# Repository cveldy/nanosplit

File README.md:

# nanosplit

Leverless (Hitbox-style) fighting game controller with a split-hand design using Cherry MX Ultra Low Profile (ULP) switches.

## About

Fully assembled, dimensions are `304 x 124 x 9.8mm` (including bolts and non-slip pads, `8.6mm` without).

Powering this device is OpenStick's excellent [GP2040-CE](https://github.com/OpenStickCommunity/GP2040-CE) gamepad firmware. Please see that repository for information about configuration, console compatibility, and all the rest.

The ultra-short scissor switches used by this controller (which I believe are primarily intended for laptop keyboards) have an extremely tactile action and are somewhat harder to depress than standard Sanwa arcade buttons. This makes their actuation feel very binary (either all-the-way down or all-the-way up), almost the complete opposite of the smooth feel of traditional arcade buttons. Experientially, I have found them to be very divisive: people either love or hate the way they feel. If possible, I recommend trying them (say, by borrowing a friend's MPress Nano at your local) before committing to a full build.

## Creation

If you want to produce one, you will need some parts.

### PCB

- 1x nanosplit PCB, created using the files in the `prod/pcb/` directory with an online PCB prototyping service. (e.g., [JLCPCB](https://jlcpcb.com/).) Productions requires assembly with SMD parts, so you'll need to include the Gerbers, BOM, and CPL files.
  - If you are unfamiliar with this process, I recommend following the PCB ordering steps from [this README](https://github.com/AlpenmeisterCustoms/MeisterboxS).
- 16x Cherry MX Ultra Low Profile Switches. (I used Tactile, but you could use Clicky if you want.)
  - I purchased mine [from this German parts supplier](https://www.reichelt.com/us/en/shop/product/cherry_mx_ultra_low_profile_rgb_pushbutton_module-335042?q=%2Fapi%2Fuser%2FcountrySelect%2Fen%2Fhttps%3A%2F%2Fwww.reichelt.com%2Fde%2Fen%2Fshop%2Fproduct%2Fcherry_mx_ultra_low_profile_rgb_pushbutton_module-335042), though they don't seem to be available at that URL anymore.

### Keycaps

- 16x [MPress Nano Caps](https://paradisearcadeshop.com/collections/mpress-nano) from Paradise Arcade Shop.

### Case

- 1x [3d-Printed Case](./prod/case/nochamfer.stl)
  - I don't personally own a 3d printer, but mine came out pretty nicely using [Craftcloud](https://craftcloud3d.com/) in ABS plastic at 60% infil (though in retrospect I may have chosen 80%).
- 1x each [Acrylic "Washer" Layer](./prod/case/acrylic_layer0_1mm.dxf) and [Acrylic Bottom Panel](./prod/case/acrylic_layer1_1mm.dxf) laser cut from `1mm` acrylic.
  - I ordered these online from [Ponoko](https://www.ponoko.com/) in clear.
- OPTIONAL: Non-slip Feet or Pads.
  - I used a few pieces cut from one of [these rolls of adhesive-backed silicon](https://www.amazon.com/dp/B09VFB7QVF).
- 8x M3-0.5 3.85mm Heat-set Threaded Inserts.
  - I ordered [these exact ones](https://www.amazon.com/dp/B077CL322T).
- 8x M3x6mm Bolts.
  - I ordered [these ultra-thin flat capped bolts](https://www.amazon.com/dp/B0C5M7M6ZM).

### Assembly

- Soldering Equipment.
- M2.5 Allen Key.

### Firmware

- The Latest [GP2040-CE Firmware for the Flatbox Rev4](https://github.com/OpenStickCommunity/GP2040-CE/releases/download/v0.7.11/GP2040-CE_0.7.11_FlatboxRev4.uf2), flashed according to the documentation.
- Pin (Button) Mapping using GP2040-CE's [Web Configurator](https://gp2040-ce.info/#/web-configurator)
  - There is a catch: the firmware assumes a default pin mapping that the nanosplit does not use. Until you've remapped the pins, you must hold down `Fn` (Function) (the bottom-most button in the central line) instead of `S2` (Start) when plugging in the controller to enter the configurator.
  - You could also short those switch contacts to ground manually if you haven't installed the switches yet when setting up the firmware.
  - After updating the pin mapping in the configurator, you'll hold `S2` to while plugging the device in to reach the configurator, like normal.
  - The correct mapping for the nanosplit is shown below.

- This controller makes `A1` (Guide), `A2` (Touchpad), `L3`, and `R3` available via a layer using the `Fn` (Function) switch (the bottom-most of the central 3).
- Shown below are the recommended function mappings, though you may prefer to use your own.

### Art

You can use [this template](./prod/art/template_A3_300dpi.psd) to place artwork into a printable template with outlines showing where to cut. The template is sized to A3 paper and set for 300dpi. Once printed and cut, the art slots between the two acrylic lays on the *bottom* of the controller.

## License

PCB and case designs licensed under [CC BY-SA 4.0](https://creativecommons.org/licenses/by/4.0/).

## Acknowledgments

- [GrooveBob](https://github.com/GroooveBob)'s [Stress](https://github.com/GroooveBob/Stress), which helped inspire this design.
- [Paradise Arcade](https://paradisearcadeshop.com/)'s [MPress Nano](https://paradisearcadeshop.com/products/mpress-nano-leverless-gaming-controller), which helped inspire this design.
- [jfedor2](https://github.com/jfedor2)'s [Flatbox](https://github.com/jfedor2/flatbox), whose RP2040 implementation I recreated. [CC BY-SA 4.0](https://creativecommons.org/licenses/by/4.0/).
- [ruiqimao](https://github.com/ruiqimao)'s [Keyboard PCB Guide](https://github.com/ruiqimao/keyboard-pcb-guide), which led me through the entire PCB creation process.
- [pashutk](https://github.com/pashutk)'s [Cherry_MX_ULP](https://github.com/pashutk/Cherry_MX_ULP) repository and links, whose footprints are present in the PCB design and whose README gave me the confidence to try hand-soldering these normally-SMD switches.
- [Sadek Baroudi](https://github.com/sadekbaroudi)'s [Keyboard Case Design](https://kbd.news/Keyboard-Case-Design-1764.html) article, which showed the process for exporting the PCB into a form usable during case design.
- [OpenStickCommunity](https://github.com/OpenStickCommunity)'s [GP2040-CE](https://github.com/OpenStickCommunity/GP2040-CE), whose firmware makes the silicon useful and whose Discord community was extremely helpful.

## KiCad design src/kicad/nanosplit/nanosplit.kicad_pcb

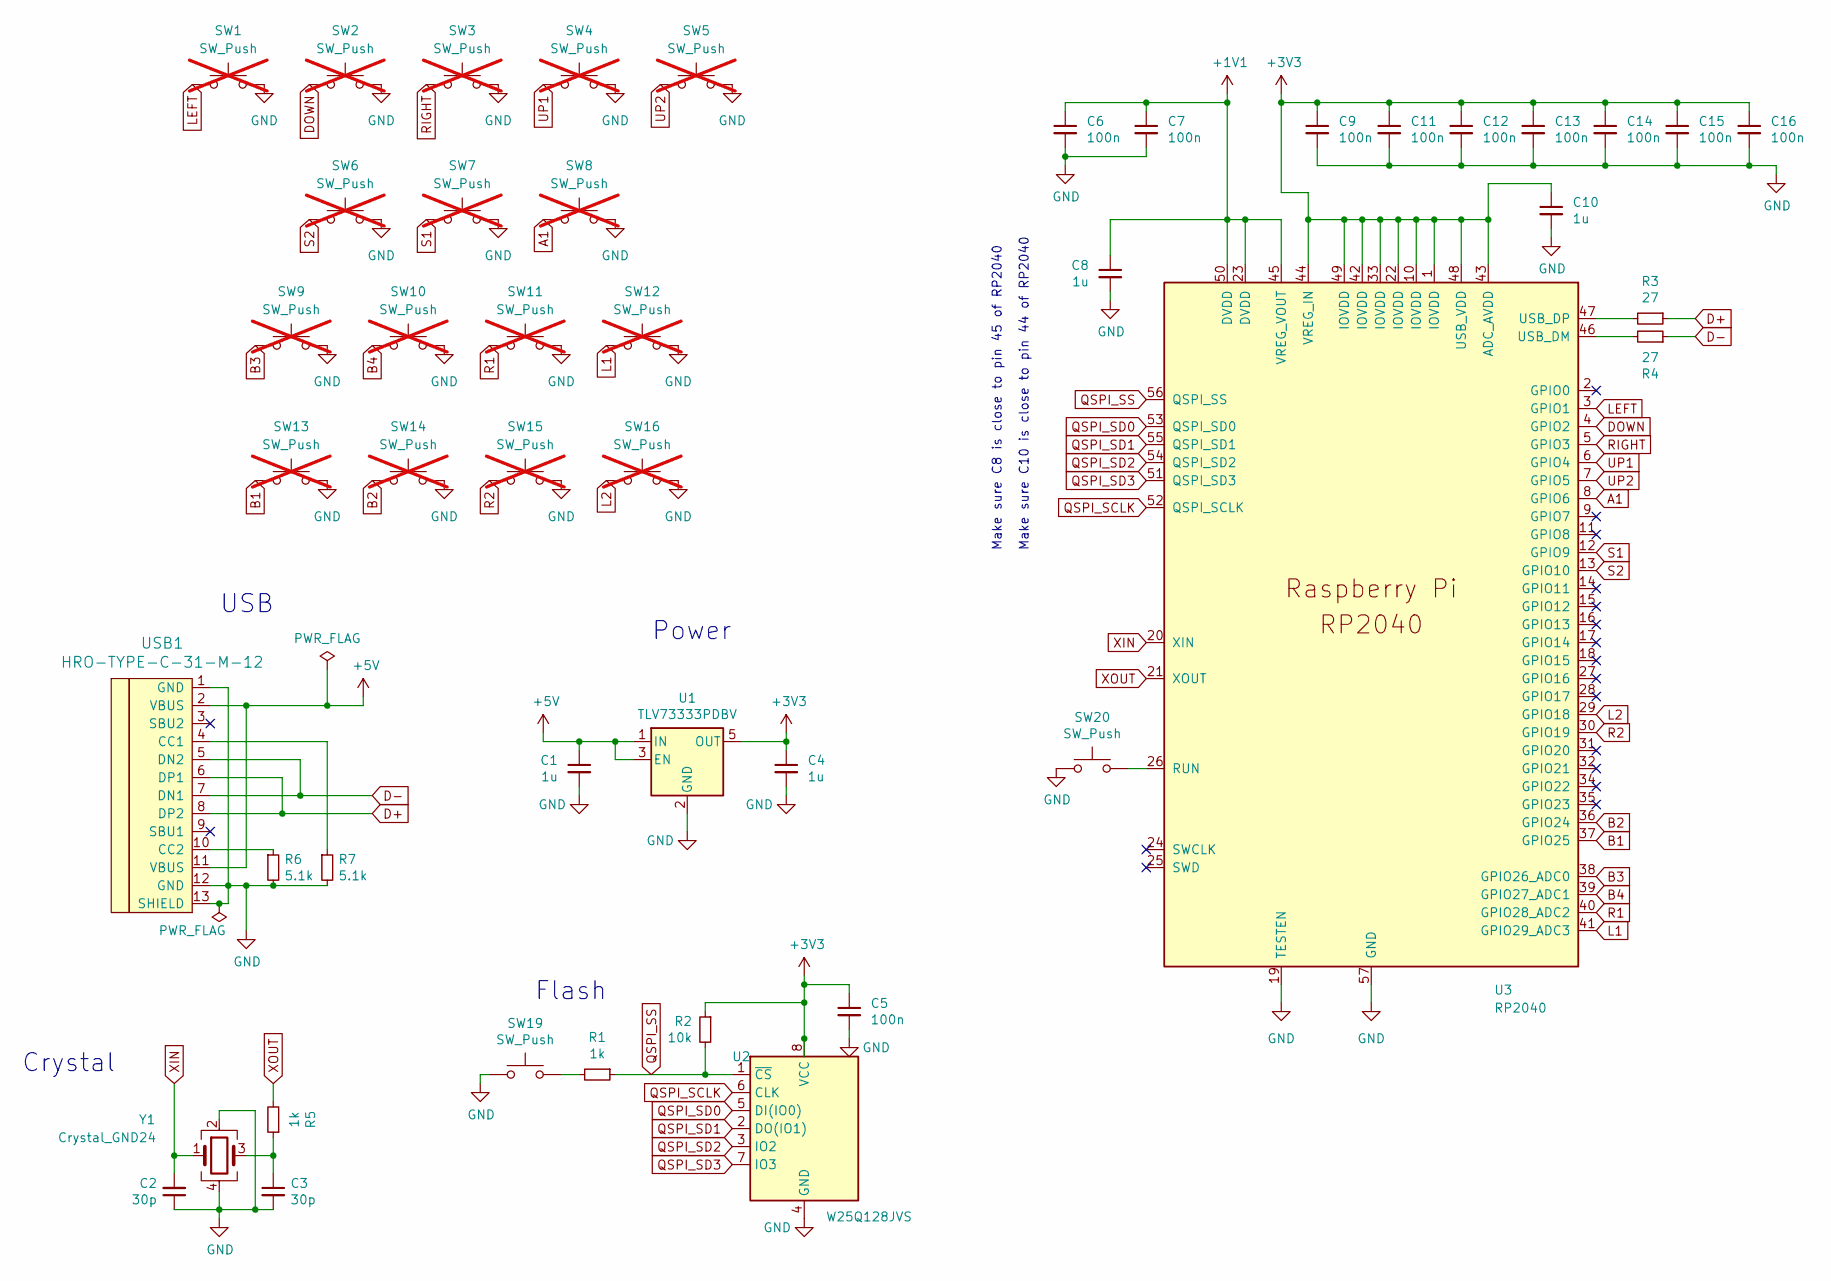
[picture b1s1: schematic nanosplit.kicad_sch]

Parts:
C1, C4, C8, C10: 1u; C_0402_1005Metric; LCSC C52923
C2, C3: 30p; C_0402_1005Metric; LCSC C1570
C5, C6, C7, C9, C11, C12, C13, C14, C15, C16: 100n; C_0402_1005Metric; LCSC C1525
R1, R5: 1k; R_0402_1005Metric; LCSC C11702
R2: 10k; R_0402_1005Metric; LCSC C25744
R3, R4: 27; R_0402_1005Metric; LCSC C138021
R6, R7: 5.1k; R_0402_1005Metric; LCSC C25905
SW1, SW2, SW3, SW4, SW5, SW6, SW7, SW8, SW9, SW10, SW11, SW12, SW13, SW14, SW15, SW16: SW_Push; Cherry_ULP_TH; not fitted
SW19, SW20: SW_Push; SW_SPST_Omron_B3FS-100xP; LCSC C271750
U1: TLV73333PDBV; SOT-23-5; LCSC C134139
U2: W25Q128JVS; SOIC-8_5.23x5.23mm_P1.27mm; LCSC C97521
U3: RP2040; RP2040-QFN-56; LCSC C2040
USB1: HRO-TYPE-C-31-M-12; HRO-TYPE-C-31-M-12-Assembly; LCSC C165948
Y1: Crystal_GND24; Crystal_SMD_3225-4Pin_3.2x2.5mm; LCSC C9002

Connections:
+1V1: C6.1, C7.1, C8.1, U3.23 (DVDD), U3.45 (VREG_VOUT), U3.50 (DVDD)
+3V3: C4.1, C5.1, C9.1, C10.1, C11.1, C12.1, C13.1, C14.1, C15.1, C16.1, R2.1, U1.5 (OUT), U2.8 (VCC), U3.1 (IOVDD), U3.10 (IOVDD), U3.22 (IOVDD), U3.33 (IOVDD), U3.42 (IOVDD), U3.43 (ADC_AVDD), U3.44 (VREG_IN), U3.48 (USB_VDD), U3.49 (IOVDD)
+5V: C1.1, U1.1 (IN), U1.3 (EN), USB1.2 (VBUS), USB1.11 (VBUS)
A1: SW8.1, U3.8 (GPIO6)
B1: SW13.1, U3.37 (GPIO25)
B2: SW14.1, U3.36 (GPIO24)
B3: SW9.1, U3.38 (GPIO26_ADC0)
B4: SW10.1, U3.39 (GPIO27_ADC1)
D+: R3.1, USB1.6 (DP1), USB1.8 (DP2)
D-: R4.1, USB1.5 (DN2), USB1.7 (DN1)
DOWN: SW2.1, U3.4 (GPIO2)
GND: C1.2, C2.1, C3.2, C4.2, C5.2, C6.2, C7.2, C8.2, C9.2, C10.2, C11.2, C12.2, C13.2, C14.2, C15.2, C16.2, R6.2, R7.2, SW1.2, SW2.2, SW3.2, SW4.2, SW5.2, SW6.2, SW7.2, SW8.2, SW9.2, SW10.2, SW11.2, SW12.2, SW13.2, SW14.2, SW15.2, SW16.2, SW19.1, SW20.1, U1.2 (GND), U2.4 (GND), U3.19 (TESTEN), U3.57 (GND), USB1.1 (GND), USB1.12 (GND), USB1.13 (SHIELD), Y1.2, Y1.4
L1: SW12.1, U3.41 (GPIO29_ADC3)
L2: SW16.1, U3.29 (GPIO18)
LEFT: SW1.1, U3.3 (GPIO1)
unnamed: C3.1, R5.1, Y1.3
unnamed: R1.2, SW19.2
unnamed: SW20.2, U3.26 (RUN)
unnamed: R4.2, U3.46 (USB_DM)
unnamed: R3.2, U3.47 (USB_DP)
unnamed: R7.1, USB1.4 (CC1)
unnamed: R6.1, USB1.10 (CC2)
QSPI_SCLK: U2.6 (CLK), U3.52 (QSPI_SCLK)
QSPI_SD0: U2.5 (DI(IO0)), U3.53 (QSPI_SD0)
QSPI_SD1: U2.2 (DO(IO1)), U3.55 (QSPI_SD1)
QSPI_SD2: U2.3 (IO2), U3.54 (QSPI_SD2)
QSPI_SD3: U2.7 (IO3), U3.51 (QSPI_SD3)
QSPI_SS: R1.1, R2.2, U2.1 (~CS), U3.56 (QSPI_SS)
R1: SW11.1, U3.40 (GPIO28_ADC2)
R2: SW15.1, U3.30 (GPIO19)
RIGHT: SW3.1, U3.5 (GPIO3)
S1: SW7.1, U3.12 (GPIO9)
S2: SW6.1, U3.13 (GPIO10)
UP1: SW4.1, U3.6 (GPIO4)
UP2: SW5.1, U3.7 (GPIO5)
XIN: C2.2, U3.20 (XIN), Y1.1
XOUT: R5.2, U3.21 (XOUT)

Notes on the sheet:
USB
Make sure C10 is close to pin 44 of RP2040
Make sure C8 is close to pin 45 of RP2040
Power
Crystal
Flash

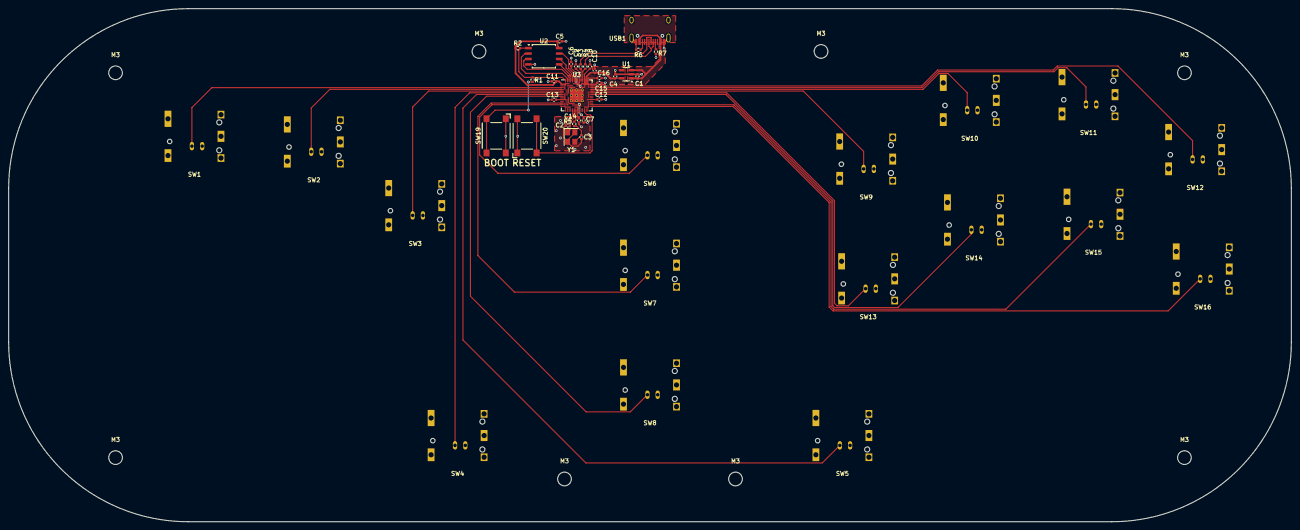
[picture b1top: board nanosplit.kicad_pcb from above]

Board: 2 copper layers, 300.0 x 120.0 mm, 54 parts (0 on the bottom side), 37 nets.

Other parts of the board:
M3, M3#2, M3#3, M3#4, M3#5, M3#6, M3#7, M3#8: MountingHole_3.2mm_M3

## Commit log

2025-01-31 Initial commit, adding important files
2025-01-31 Added mention of license to README
2025-07-13 Added PCB production files!
2025-08-04 First versions of case files.
2025-09-07 Final assembled version. (TODO: Art and an image for the README)
2025-09-07 Updated About section and Acknowledgments
2025-09-07 README typo fixes
2025-09-07 Added controller image
2025-09-09 Added art template
